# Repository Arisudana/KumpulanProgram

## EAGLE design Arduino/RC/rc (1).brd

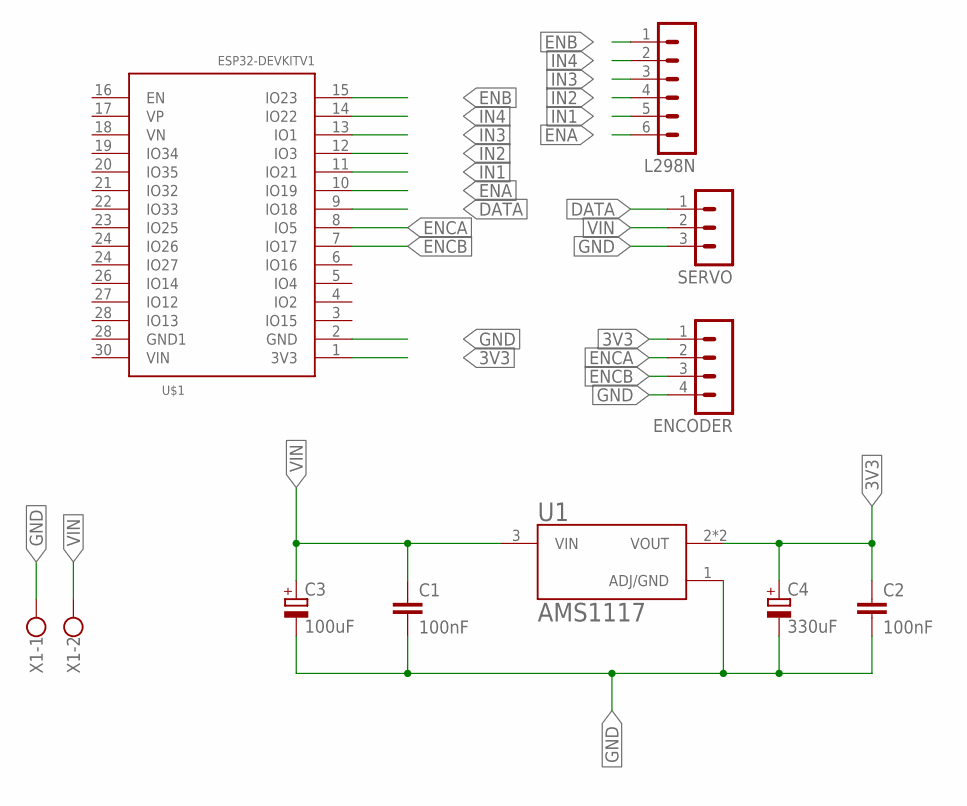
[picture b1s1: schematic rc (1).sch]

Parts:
C1, C2: 100nF; C0805
C3: 100uF; CT6032
C4: 330uF; CT6032
ENCODER: MA04-1
L298N: MA06-1
SERVO: MA03-1
U1: AMS1117; SOT229P700X180-4N
U$1: ESP32DEVKITV1; ESP32-DEVKITV1
X1: W237-102

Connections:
3V3: C2.1, C4.+, ENCODER.1, U1.2 (VOUT), U1.4 (VOUT), U$1.1 (3V3)
DATA: SERVO.1, U$1.9 (IO18)
ENA: L298N.6, U$1.10 (IO19)
ENB: L298N.1, U$1.15 (IO23)
ENCA: ENCODER.2, U$1.8 (IO5)
ENCB: ENCODER.3, U$1.7 (IO17)
GND: C1.2, C2.2, C3.-, C4.-, ENCODER.4, SERVO.3, U1.1 (ADJ/GND), U$1.2 (GND), X1.1
IN1: L298N.5, U$1.11 (IO21)
IN2: L298N.4, U$1.12 (IO3)
IN3: L298N.3, U$1.13 (IO1)
IN4: L298N.2, U$1.14 (IO22)
VIN: C1.1, C3.+, SERVO.2, U1.3 (VIN), X1.2

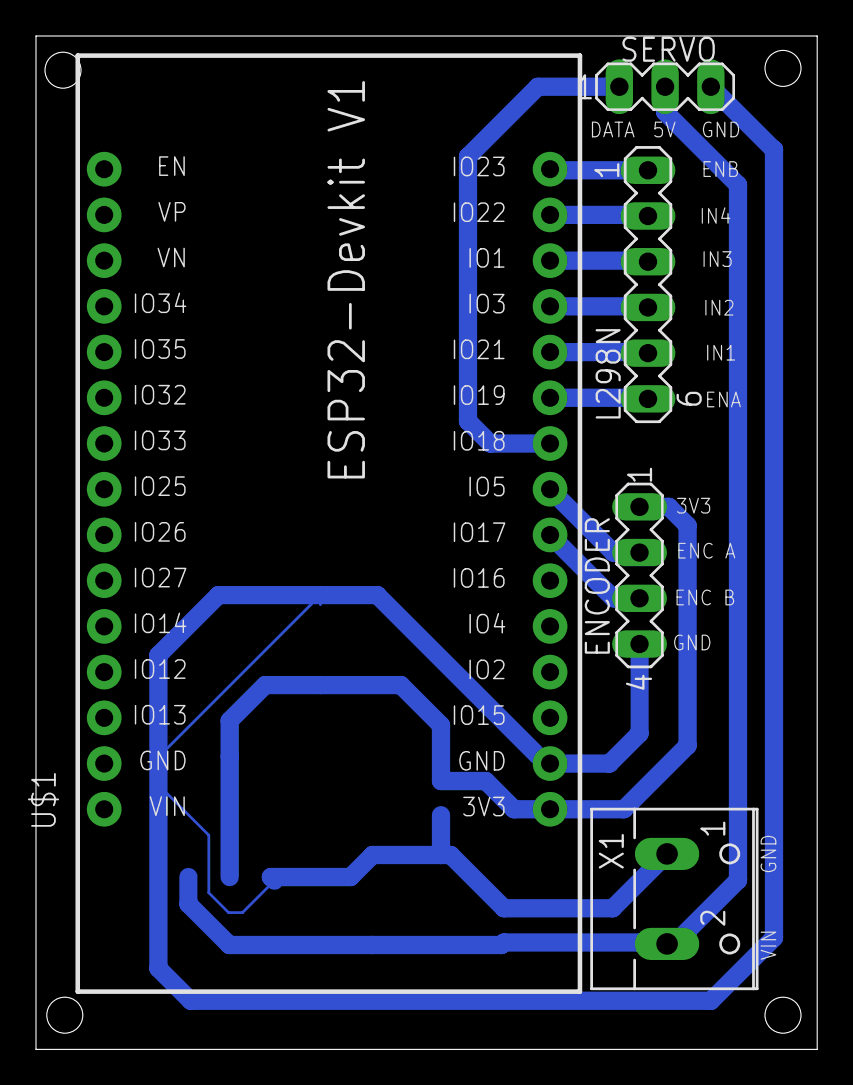
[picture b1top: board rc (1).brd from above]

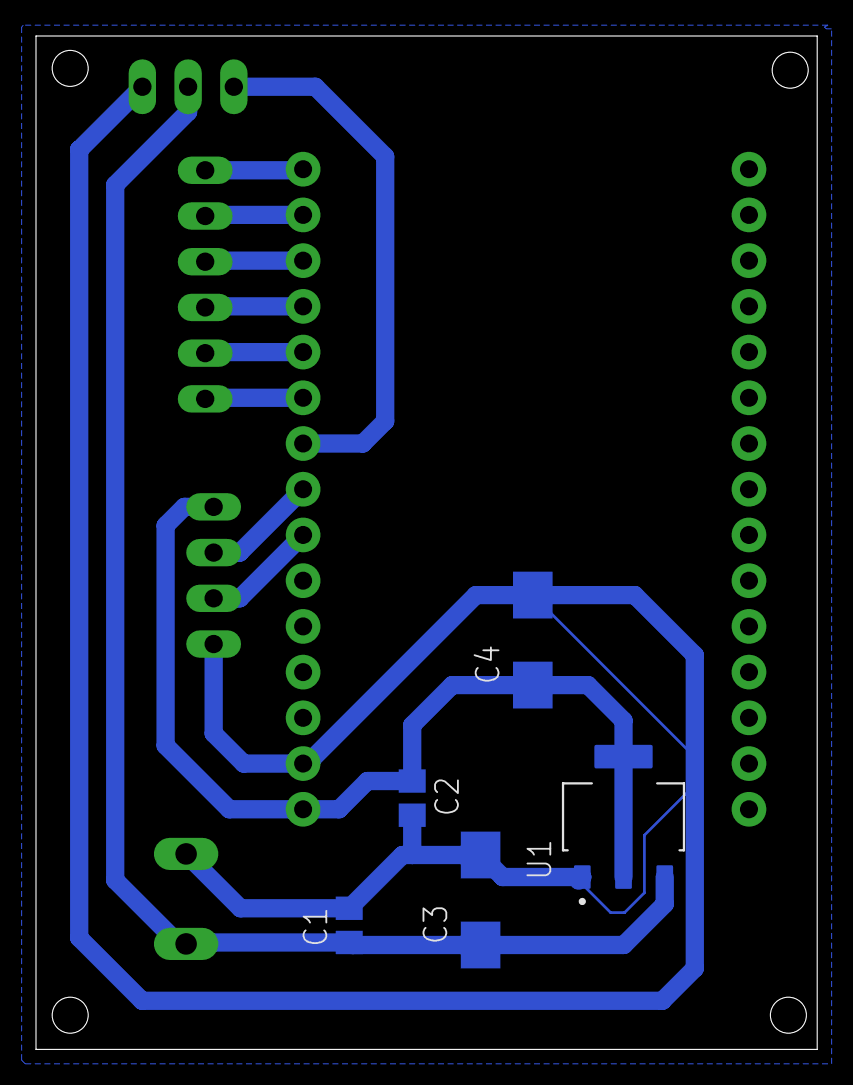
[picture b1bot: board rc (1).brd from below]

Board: 2 copper layers, 43.4 x 56.3 mm, 10 parts (5 on the bottom side), 12 nets.
